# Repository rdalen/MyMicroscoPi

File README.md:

# MyMicroscoPi
This DIY microscope design combines many of my hobbies; Lego, electronics, 3D printing, Arduino, Raspberry Pi, etc.

My design is a remix of a great and well documented [design of Yuksel Temizon](https://github.com/IBM/MicroscoPy).
My version is also built of LEGO bricks, but uses also LEGO Technic beams because they are light and strong.
For capturing images it uses a Raspberry Pi 3B+ with an 8MP camera and modified lens. The six stepper motors for the camera & sample movements and the power LED for illumination are controlled by two PCB's with an [Arduino Pro mini](https://www.arduino.cc/en/Guide/ArduinoProMini) on each PCB.
* One PCB (Mainboard) contains all the driver hardware for the steppers and power LED
* The other PCB (Controller board) contains the human interface elements for controlling the microscope. Such as; Three joysticks to control the X, Y, Rotary, Tilt (Camera-angle), Magnitude and Focus, a Rotary encoder to control the Power LED and a small OLED display to indicate the brightness of the power LED

I used the 3D printed LEGO gears and adapters of the [original design](https://github.com/IBM/MicroscoPy)

So, after many hours of building pleasure, I'm going to do some nice experiments now

### Information & Documentation
* [Hackster.io project; IBM Researcher Makes a Microscope Using LEGO, Arduino, and Raspberry Pi](https://www.hackster.io/news/ibm-researcher-makes-a-microscope-using-lego-arduino-and-raspberry-pi-cbc58cb69a20?utm_source=Hackster+Marketing&utm_campaign=7e2e7b20ec-EMAIL_CAMPAIGN_2019_02_14_02_53_COPY_01&utm_medium=email&utm_term=0_86d76c4d75-7e2e7b20ec-144680307&mc_cid=7e2e7b20ec&mc_eid=ea3c09e980)
* [Github IBM/MicroscoPy](https://github.com/IBM/MicroscoPy)
* [YouTube link MyMicroscoPi](https://youtu.be/3TL11zC14ig)

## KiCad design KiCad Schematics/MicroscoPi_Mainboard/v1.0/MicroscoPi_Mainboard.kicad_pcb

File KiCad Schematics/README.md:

# KiCad
* Both PCB's are made with the version V1.0 design
* Modifications on these PCB's are incorporated in the version V2.0 schematics
* Hence; V2.0 has no PCB-update!!
* The gerber file of the Controllerboard V1.0 consists of a panel with 2 PCB's

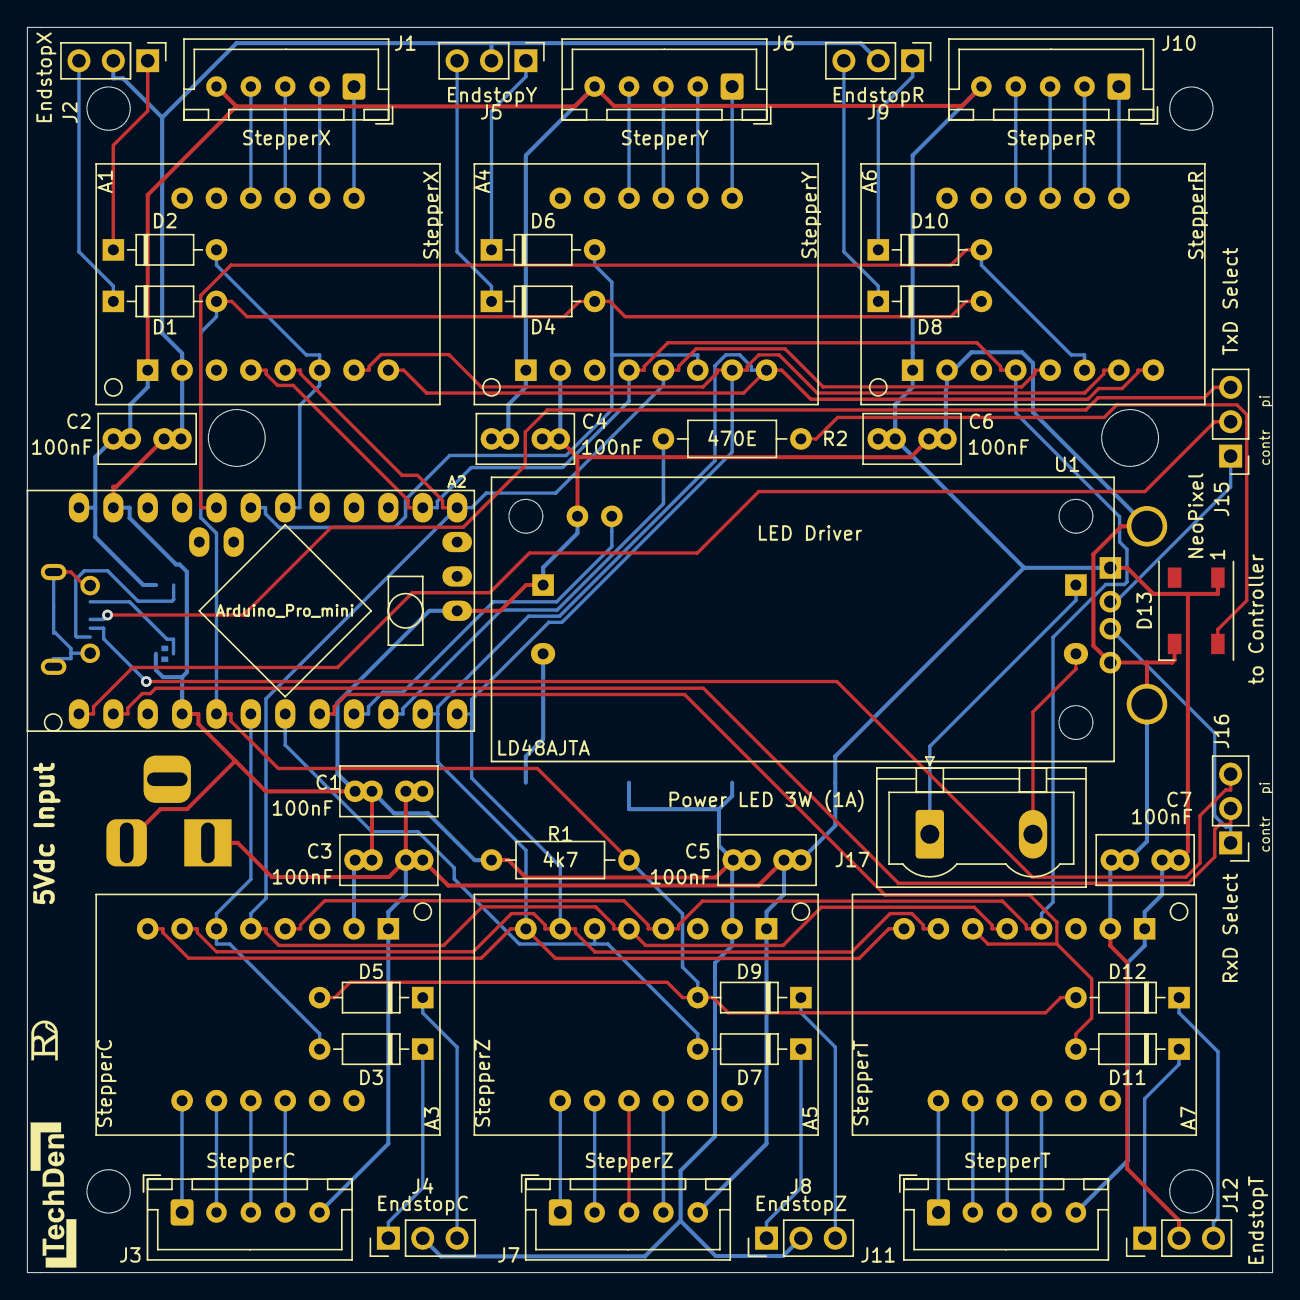
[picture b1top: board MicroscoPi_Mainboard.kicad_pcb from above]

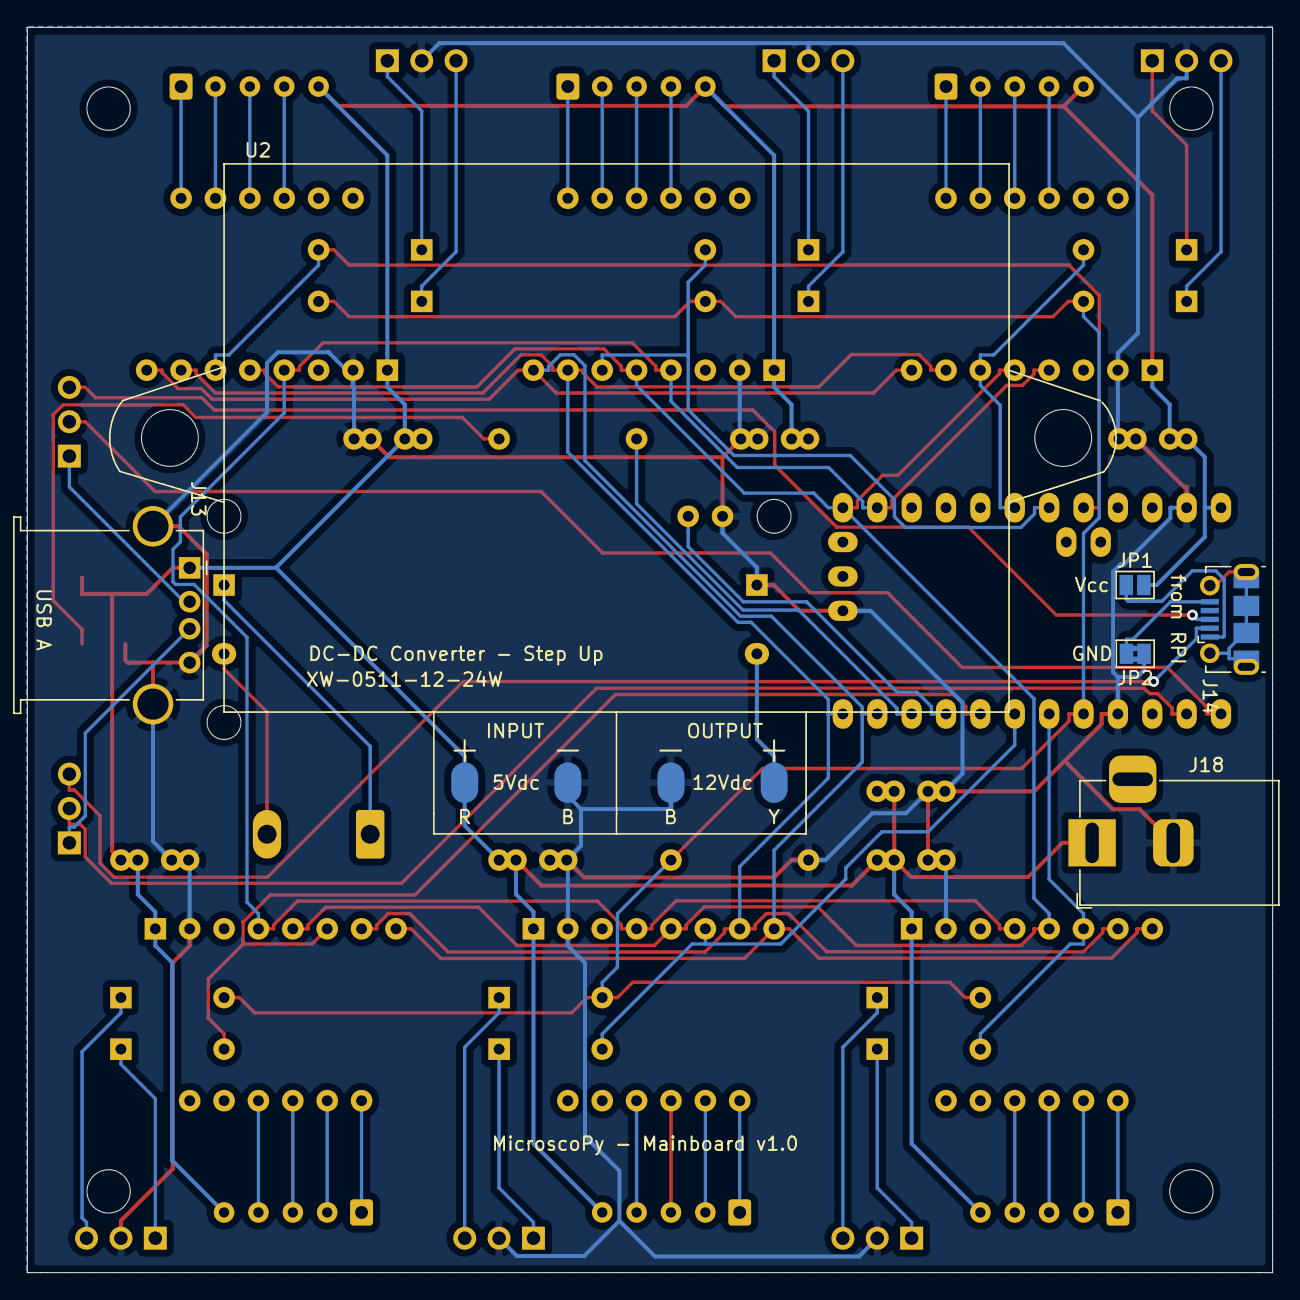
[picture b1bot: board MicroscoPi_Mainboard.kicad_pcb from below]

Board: 2 copper layers, 92.0 x 92.0 mm, 53 parts (6 on the bottom side), 63 nets.

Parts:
A1: StepperX; Adafruit_Breakout_DRV8825
A2: Arduino_Pro_mini; Arduino_pro_mini_v2
A3: StepperC; Adafruit_Breakout_DRV8825
A4: StepperY; Adafruit_Breakout_DRV8825
A5: StepperZ; Adafruit_Breakout_DRV8825
A6: StepperR; Adafruit_Breakout_DRV8825
A7: StepperT; Adafruit_Breakout_DRV8825
C1, C2, C3, C4, C5, C6, C7: 100nF; C_Rect_L7.0mm_W3.5mm_P2.50mm_P5.00mm
D1, D2, D3, D4, D5, D6, D7, D8, D9, D10, D11, D12: DUS; D_DO-35_SOD27_P7.62mm_Horizontal
D13: WS2812B; LED_WS2812B_PLCC4_5.0x5.0mm_P3.2mm
J1: StepperX; JST_XH_B5B-XH-A_1x05_P2.54mm_Vertical
J2: EndstopX; PinHeader_1x03_P2.54mm_Vertical
J3: StepperC; JST_XH_B5B-XH-A_1x05_P2.54mm_Vertical
J4: EndstopC; PinHeader_1x03_P2.54mm_Vertical
J5: EndstopY; PinHeader_1x03_P2.54mm_Vertical
J6: StepperY; JST_XH_B5B-XH-A_1x05_P2.54mm_Vertical
J7: StepperZ; JST_XH_B5B-XH-A_1x05_P2.54mm_Vertical
J8: EndstopZ; PinHeader_1x03_P2.54mm_Vertical
J9: EndstopR; PinHeader_1x03_P2.54mm_Vertical
J10: StepperR; JST_XH_B5B-XH-A_1x05_P2.54mm_Vertical
J11: StepperT; JST_XH_B5B-XH-A_1x05_P2.54mm_Vertical
J12: EndstopT; PinHeader_1x03_P2.54mm_Vertical
J13: USB A; USB_A_Stewart_SS-52100-001_Horizontal
J14: from RPI; USB_Micro-B_Molex-105017-0001
J15: TxD Select; PinHeader_1x03_P2.54mm_Vertical
J16: RxD Select; PinHeader_1x03_P2.54mm_Vertical
J17: Power LED 3W (1A); PhoenixContact_GMSTBVA_2,5_2-G-7,62_1x02_P7.62mm_Vertical
J18: Power Jack; BarrelJack_Horizontal
JP1: Vcc; SolderJumper-2_P1.3mm_Open_Pad1.0x1.5mm
JP2: GND; SolderJumper-2_P1.3mm_Bridged2Bar_Pad1.0x1.5mm
L1: Logo-TechDen; TechDen Logo - inverted
L2: Logo-RvD; RvD Logo inverted small
R1: 4k7; R_Axial_DIN0207_L6.3mm_D2.5mm_P10.16mm_Horizontal
R2: 470E; R_Axial_DIN0207_L6.3mm_D2.5mm_P10.16mm_Horizontal
U1: LD48AJTA
U2: XW-0511-12-24W

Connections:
+12V: U1.2, U2.4
/GPIO02: A2.5, D1.2, D4.2, D5.2, D8.2, D9.2, D12.2, R1.1
/GPIO03: A2.6, A3.6, D3.2
/GPIO04: A2.7, A5.6, D7.2
/GPIO05: A2.8, A7.6, D11.2
/GPIO06: A2.9, U1.6
/GPIO07: A2.10, R2.1
/GPIO08: A1.8, A2.11, A3.8, A4.8, A5.8, A6.8, A7.8
/GPIO09: A1.7, A2.12, A3.7, A4.7, A5.7, A6.7, A7.7
/GPIO10: A1.5, A2.13, A3.5, A4.5, A5.5, A6.5, A7.5
/GPIO11: A1.4, A2.14, A3.4, A4.4, A5.4, A6.4, A7.4
/GPIOA1: A1.6, A2.18, D2.2
/GPIOA2: A2.19, A4.6, D6.2
/GPIOA3: A2.20, A6.6, D10.2
/RxD: A2.2, J16.2
/RxD_Contr: J13.3, J16.1
/RxD_RPI: J14.2, J16.3
/TxD: A2.1, J15.2
/TxD_Contr: J13.2, J15.1
/TxD_RPI: J14.3, J15.3
GND: A1.2, A2.4, A2.23, A2.35, A3.2, A4.2, A5.2, A6.2, A7.2, C1.2, C2.2, C3.2, C4.2, C5.2, C6.2, C7.2, D13.3, J2.2, J4.2, J5.2, J8.2, J9.2, J12.2, J13.4, J13.5, J18.2, JP2.1, R1.2, U1.1, U1.5, U2.2, U2.3
unnamed: A1.10, J1.1
unnamed: A1.11, J1.2
unnamed: A1.12, J1.3
unnamed: A1.13, J1.4
unnamed: A3.10, J3.1
unnamed: A3.11, J3.2
unnamed: A3.12, J3.3
unnamed: A3.13, J3.4
unnamed: A4.10, J6.1
unnamed: A4.11, J6.2
unnamed: A4.12, J6.3
unnamed: A4.13, J6.4
unnamed: A5.10, J7.1
unnamed: A5.11, J7.2
unnamed: A5.12, J7.3
unnamed: A5.13, J7.4
unnamed: A6.10, J10.1
unnamed: A6.11, J10.2
unnamed: A6.12, J10.3
unnamed: A6.13, J10.4
unnamed: A7.10, J11.1
unnamed: A7.11, J11.2
unnamed: A7.12, J11.3
unnamed: A7.13, J11.4
unnamed: D1.1, J2.3
unnamed: D2.1, J2.1
unnamed: D3.1, J4.1
unnamed: D4.1, J5.3
unnamed: D5.1, J4.3
unnamed: D6.1, J5.1
unnamed: D7.1, J8.1
unnamed: D8.1, J9.3
unnamed: D9.1, J8.3
unnamed: D10.1, J9.1
unnamed: D11.1, J12.1
unnamed: D12.1, J12.3
unnamed: D13.4, R2.2
unnamed: J14.1, JP1.1
unnamed: J14.5, JP2.2
unnamed: J17.1, U1.3
unnamed: J17.2, U1.4
VCC: A1.1, A2.24, A3.1, A4.1, A5.1, A6.1, A7.1, C1.1, C2.1, C3.1, C4.1, C5.1, C6.1, C7.1, D13.1, J1.5, J3.5, J6.5, J7.5, J10.5, J11.5, J13.1, J18.1, JP1.2, U2.1

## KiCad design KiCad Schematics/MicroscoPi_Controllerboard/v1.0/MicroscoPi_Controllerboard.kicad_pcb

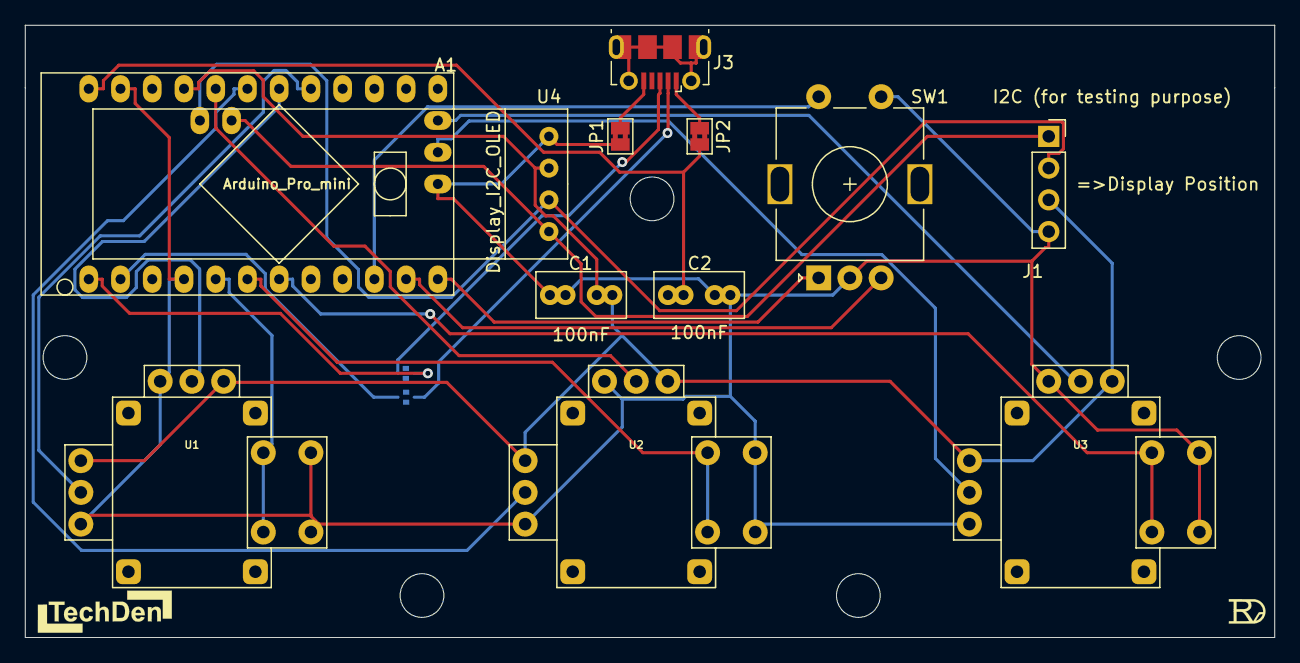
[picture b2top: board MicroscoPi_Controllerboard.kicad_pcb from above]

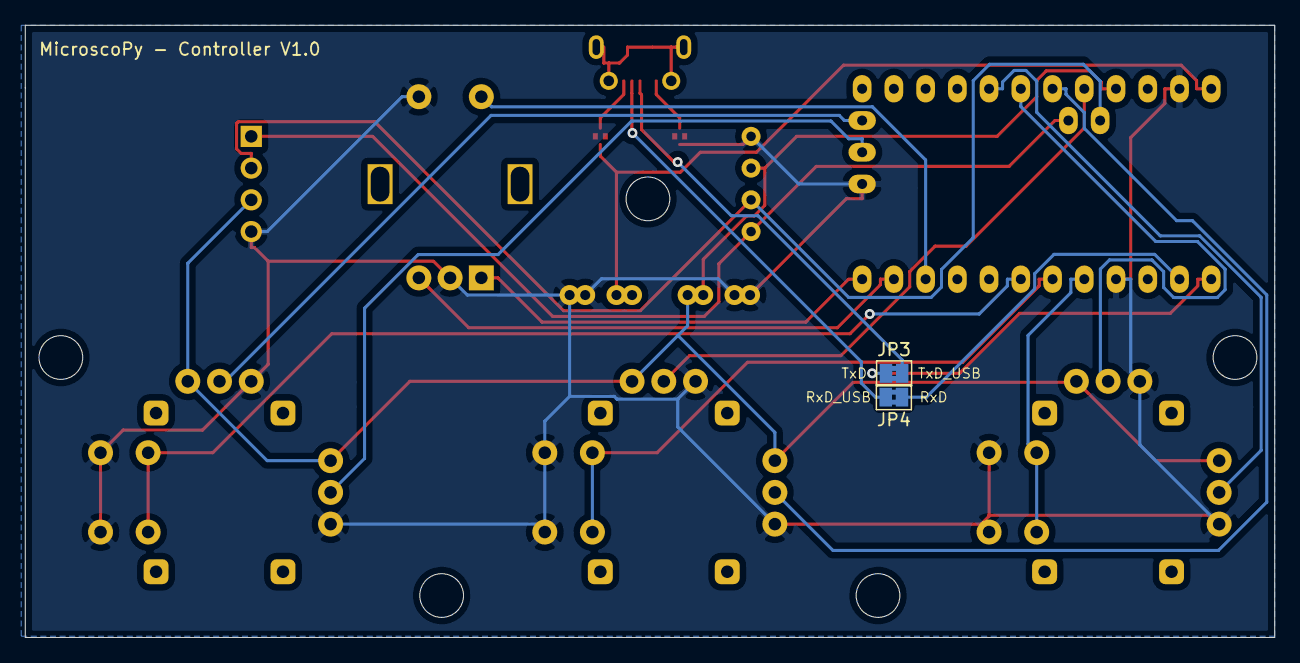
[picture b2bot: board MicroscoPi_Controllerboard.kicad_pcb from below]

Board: 2 copper layers, 100.0 x 49.0 mm, 16 parts (2 on the bottom side), 23 nets.

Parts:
A1: Arduino_Pro_mini; Arduino_pro_mini_v2
C1, C2: 100nF; C_Rect_L7.0mm_W3.5mm_P2.50mm_P5.00mm
J1: I2C (for testing purpose); PinSocket_1x04_P2.54mm_Vertical
J3: Power in; USB_Micro-B_Molex-105017-0001
JP1, JP2, JP3, JP4: SolderJumper_2_Bridged; SolderJumper-2_P1.3mm_Bridged2Bar_Pad1.0x1.5mm
L1: Logo-TechDen; TechDen Logo - inverted
L2: Logo-RvD; RvD Logo inverted small
SW1: Rotary_Encoder_Switch; RotaryEncoder_Alps_EC11E-Switch_Vertical_H20mm
U1, U2, U3: JOYSTICK_BUTTON; Joystick_w_Button
U4: Display_I2C_OLED; SSD1306_OLED-0.91-128x32

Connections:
+5V: A1.21, C1.1, J1.3, U1.X1, U1.Y1, U2.X1, U2.Y1, U3.X1, U3.Y1, U4.3
/BUTTON1: A1.5, U1.SWa
/BUTTON2: A1.6, U2.SWa
/BUTTON3: A1.7, U3.SWa
/BUTTON4: A1.10, SW1.S2
/C: A1.20, U2.X2
/CLK: A1.12, SW1.A
/DT: A1.11, SW1.B
/GPIOA0: A1.17, U1.Y2
/GPIOA1: A1.18, U1.X2
/GPIOA2: A1.19, U2.Y2
/GPIOA6: A1.34, U3.Y2
/GPIOA7: A1.33, U3.X2
/RxD: A1.2, JP4.1
/RxD_USB: J3.2, JP4.2
/SCL: A1.31, J1.2, U4.2
/SDA: A1.32, J1.1, U4.1
/TxD: A1.1, JP3.2
/TxD_USB: J3.3, JP3.1
GND: A1.4, A1.23, A1.35, C1.2, C2.2, J1.4, JP1.2, SW1.C, SW1.S1, U1.SWb, U1.X3, U1.Y3, U2.SWb, U2.X3, U2.Y3, U3.SWb, U3.X3, U3.Y3, U4.4
unnamed: J3.1, JP2.1
unnamed: J3.5, JP1.1
VCC: A1.24, C2.1, JP2.2

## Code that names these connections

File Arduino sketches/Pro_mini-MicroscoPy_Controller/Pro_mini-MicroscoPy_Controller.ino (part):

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#define joystickC A3
#define joystickR A7
#define joystickT A6
#define BUTTON1 2 //Button Joystick U1
#define BUTTON2 3 //Button Joystick U2 
#define BUTTON3 4 //Button Joystick U3 
#define RE_DT 8  // Rotary encoder signal DT (output A)
#define RE_CLK 9  // Rotary encoder signal CLK (output B)
#define RE_BUTTON 7 // Rotary encoder button | active LOW
#define BUTTON4 RE_BUTTON // ... also known as BUTTON4
#define RE_MAX 40 // Count value of one rotation of the   Rotary encoder

// potentiometer for the LED intensity
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  pinMode(joystickC, INPUT); // Focus stepper
  pinMode(joystickR, INPUT); // Rotatie stepper
  pinMode(joystickT, INPUT); // Tilt stepper
  pinMode(BUTTON1, INPUT_PULLUP); //Joystick X/Y button | active LOW
  pinMode(BUTTON2, INPUT_PULLUP); //Joystick Z/C button | active LOW
  pinMode(BUTTON3, INPUT_PULLUP); //Joystick R/T button | active LOW 
  pinMode(BUTTON4, INPUT_PULLUP);  //Rotary encoder button | active LOW
  pinMode (RE_DT,INPUT_PULLUP); // Rotary encoder DT signal
  pinMode (RE_CLK,INPUT_PULLUP); // Rotary encoder CLK signal
//  pinMode(potLED, INPUT);
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
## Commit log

2020-10-24 V1.0 - Initial version
2020-10-24 Sketch folder added
2020-10-25 The entire project
2020-10-25 BOM lists added

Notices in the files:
Arduino sketches/Pro_mini-MicroscoPy_Controller/Pro_mini-MicroscoPy_Controller.ino:
include <Adafruit_GFX.h> // needed for the OLED // Copyright (c) 2012 Adafruit Industries.  All rights reserved.
include <Adafruit_SSD1306.h> // needed for the OLED // Copyright (c) 2012 Adafruit Industries.  All rights reserved.
